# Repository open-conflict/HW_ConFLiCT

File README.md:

HW_ConFLiCT
===========

ConFLiCT

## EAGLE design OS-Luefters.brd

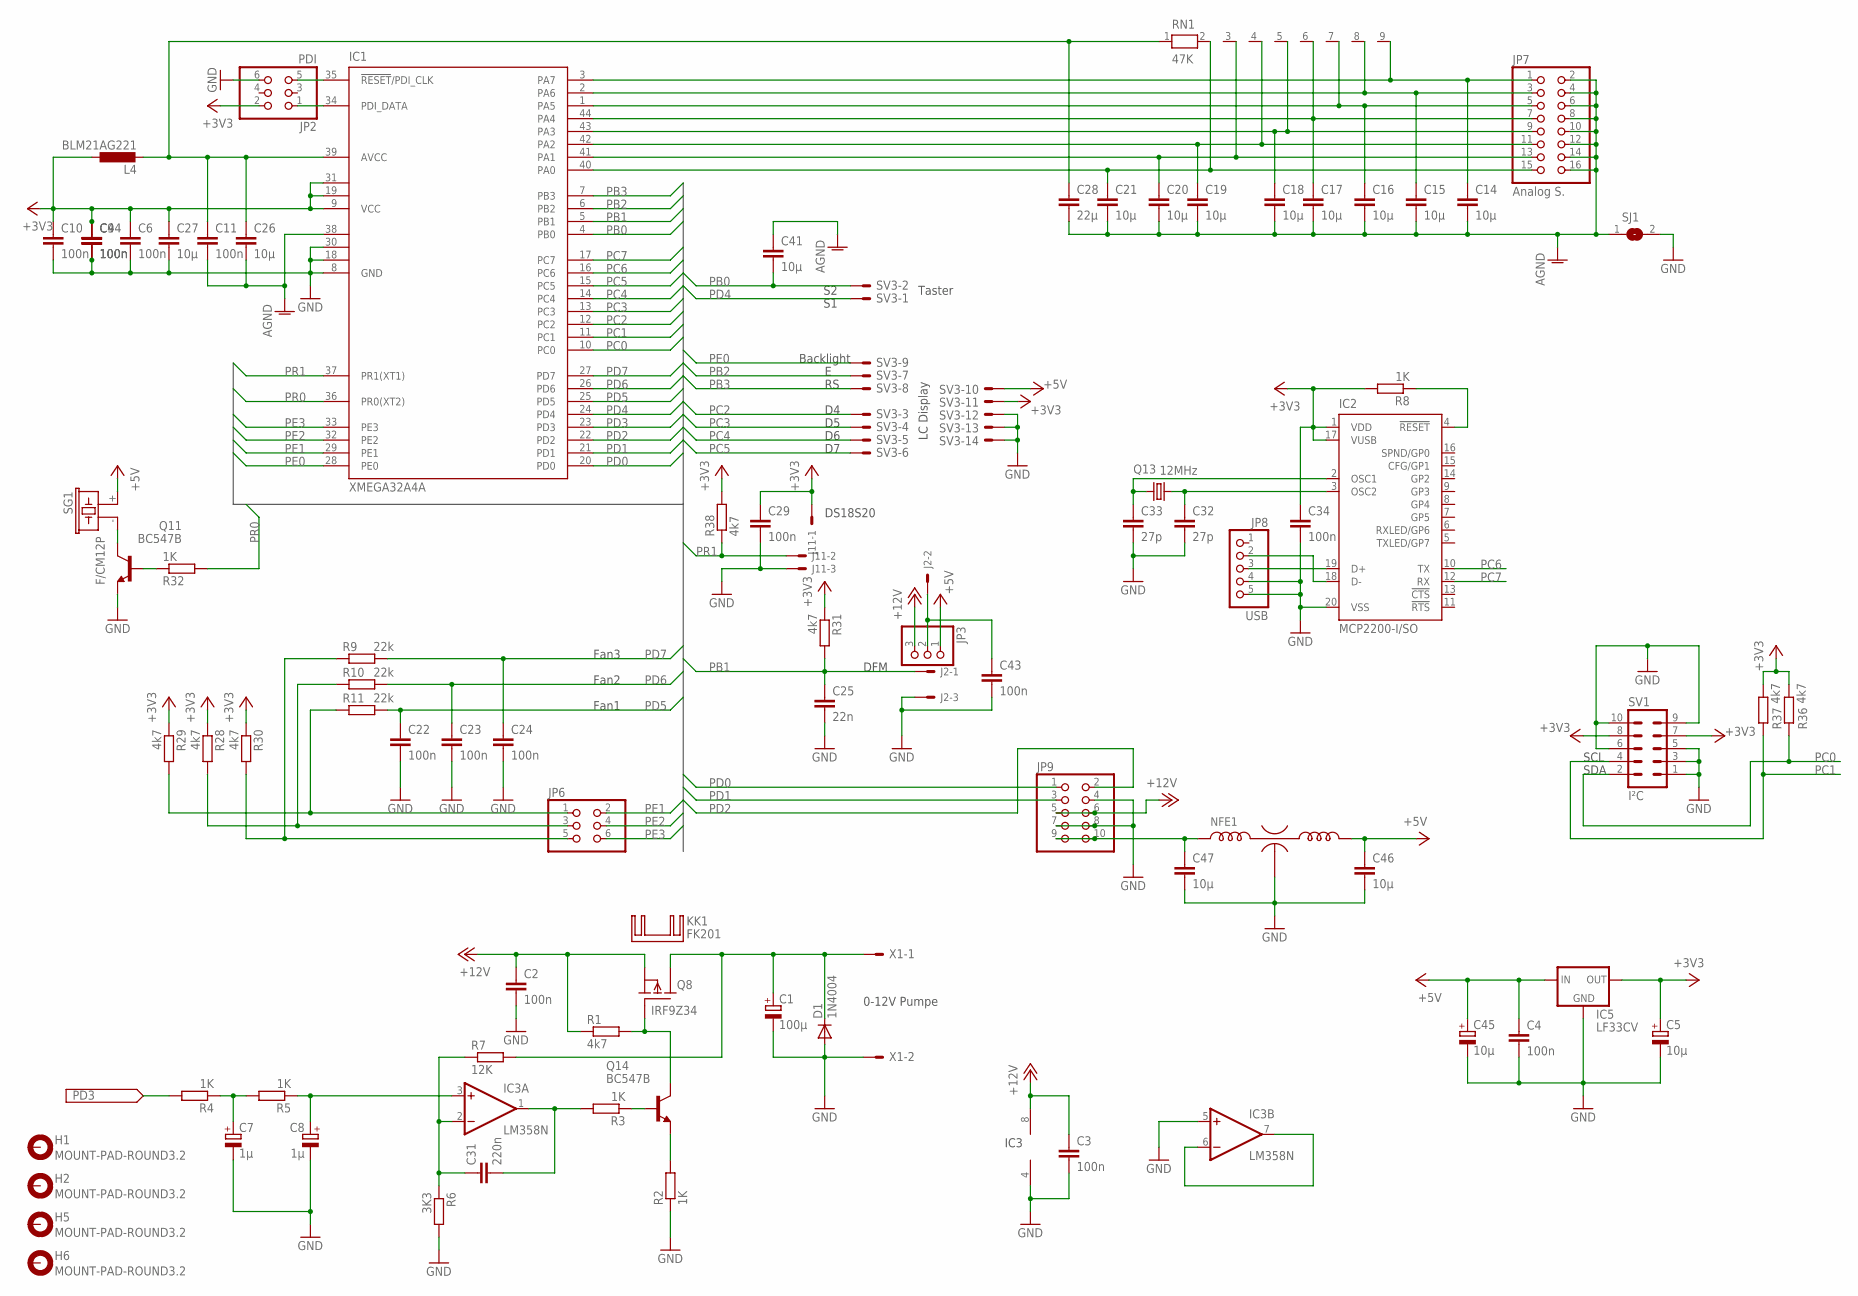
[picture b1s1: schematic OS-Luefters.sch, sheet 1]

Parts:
C1: 100µ; E2,5-7
C2, C3, C4, C22, C23, C24, C34, C43: 100n; C050-025X075
C5, C45: 10µ; E2-5
C6, C9, C10, C11, C29, C44: 100n; C0805K
C7, C8: 1µ; E2-5
C14, C15, C16, C17, C18, C19, C20, C21, C26, C27, C41, C46, C47: 10µ; C0805K
C25: 22n; C050-025X075
C28: 22µ; C0805K
C31: 220n; C050-025X075
C32, C33: 27p; C025-024X044
D1: 1N4004; DO41-10
H1, H2, H5, H6: MOUNT-PAD-ROUND3.2; 3,2-PAD
IC1: XMEGA32A4A; TQFP44
IC2: MCP2200-I/SO; SO-20W
IC3: LM358N; DIL08
IC5: LF33CV; 78XXL
J2, J11: 22-05-7038-03; 7395-03
JP2: PDI; 2X03
JP3: PINHD-1X3/90; 1X03/90
JP6: PINHD-2X3; 2X03
JP7: Analog S.; 2X08/90
JP8: USB; 1X05/90
JP9: PINHD-2X5; 2X05
KK1: FK201
L4: BLM21AG221; L2825P
NFE1: NFE61; 2706
Q8: IRF9Z34; TO220S
Q11, Q14: BC547B; TO92
Q13: 12MHz; HC49U-V
R1, R28, R29, R30, R31, R36, R37, R38: 4k7; 0207/10
R2, R3, R4, R5, R8, R32: 1K; 0207/10
R6: 3K3; 0207/10
R7: 12K; 0207/10
R9, R10, R11: 22k; 0207/10
RN1: 47K; RN-9
SG1: F/CM12P
SJ1: SJ
SV1: I²C; ML10
SV3: ML14E; ML14
X1: AKL18X-02W-NO; AKL182-02-NO

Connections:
+3V3: C5.+, C6.1, C9.1, C10.1, C27.1, C29.1, C34.1, C44.1, IC1.9 (VCC), IC1.19 (VCC1), IC1.31 (VCC2), IC2.1 (VDD), IC2.17 (VUSB), IC5.OUT, J11.1, JP2.2, L4.1, R8.2, R28.1, R29.1, R30.1, R31.1, R36.2, R37.2, R38.2, SV1.7, SV1.8, SV3.11
+5V: C4.1, C45.+, C46.1, IC5.IN, JP3.1, NFE1.OUT, SG1.+ (1), SV3.10
+12V: C2.1, C3.1, IC3.8 (V+), JP3.3, JP9.5, JP9.6, Q8.3 (S), R1.1
AGND: C11.2, C14.2, C15.2, C16.2, C17.2, C18.2, C19.2, C20.2, C21.2, C26.2, C28.2, C41.1, IC1.38 (GND3), JP7.2, JP7.4, JP7.6, JP7.8, JP7.10, JP7.12, JP7.14, JP7.16, SJ1.1
GND: C1.-, C2.2, C3.2, C4.2, C5.-, C6.2, C7.-, C8.-, C9.2, C10.2, C22.2, C23.2, C24.2, C25.2, C27.2, C29.2, C32.2, C33.2, C34.2, C43.2, C44.2, C45.-, C46.2, C47.2, D1.A, IC1.8 (GND), IC1.18 (GND1), IC1.30 (GND2), IC2.20 (VSS), IC3.4 (V-), IC3.5 (+IN), IC5.GND, J2.3, J11.3, JP2.6, JP8.4, JP8.5, JP9.4, JP9.7, JP9.8, NFE1.GND, Q11.1 (E), R2.1, R6.2, SJ1.2, SV1.1, SV1.3, SV1.5, SV1.6, SV1.9, SV1.10, SV3.12, SV3.13, SV3.14, X1.P$2
unnamed: C1.+, D1.C, Q8.2 (D), R7.2, X1.P$1
unnamed: IC3.6 (-IN), IC3.7 (OUT)
unnamed: C43.1, J2.2, JP3.2
unnamed: C7.+, R4.1, R5.2
unnamed: Q8.1 (G), Q14.3 (C), R1.2
unnamed: Q14.1 (E), R2.2
unnamed: C8.+, IC3.3 (+IN), R5.1
unnamed: IC1.34 (PDI_DATA), JP2.1
unnamed: IC1.35 (!RESET!/PDI_CLK), JP2.5
unnamed: C14.1, IC1.3 (PA7), JP7.1, RN1.9
unnamed: C15.1, IC1.2 (PA6), JP7.3, RN1.8
unnamed: C16.1, IC1.1 (PA5), JP7.5, RN1.7
unnamed: C17.1, IC1.44 (PA4), JP7.7, RN1.6
unnamed: C18.1, IC1.43 (PA3), JP7.9, RN1.5
unnamed: C19.1, IC1.42 (PA2), JP7.11, RN1.4
unnamed: C20.1, IC1.41 (PA1), JP7.13, RN1.3
unnamed: C21.1, IC1.40 (PA0), JP7.15, RN1.2
unnamed: Q11.3 (C), SG1.- (2)
unnamed: Q11.2 (B), R32.1
unnamed: C47.1, JP9.9, JP9.10, NFE1.IN
unnamed: Q14.2 (B), R3.1
unnamed: C31.2, IC3.1 (OUT), R3.2
unnamed: C31.1, IC3.2 (-IN), R6.1, R7.1
unnamed: C11.1, C26.1, C28.1, IC1.39 (AVCC), L4.2, RN1.1
unnamed: JP6.5, R9.1, R30.2
unnamed: C32.1, IC2.3 (OSC2), Q13.2
unnamed: C33.1, IC2.2 (OSC1), Q13.1
unnamed: JP6.3, R10.1, R28.2
unnamed: IC2.18 (D-), JP8.2
unnamed: IC2.19 (D+), JP8.3
unnamed: IC2.4 (!RESET), R8.1
unnamed: JP6.1, R11.1, R29.2
PB0: C41.2, IC1.4 (PB0), SV3.2
PB1: C25.1, IC1.5 (PB1), J2.1, R31.2
PB2: IC1.6 (PB2), SV3.7
PB3: IC1.7 (PB3), SV3.8
PC0: IC1.10 (PC0), R36.1, SV1.2
PC1: IC1.11 (PC1), R37.1, SV1.4
PC2: IC1.12 (PC2), SV3.3
PC3: IC1.13 (PC3), SV3.4
PC4: IC1.14 (PC4), SV3.5
PC5: IC1.15 (PC5), SV3.6
PC6: IC1.16 (PC6), IC2.10 (TX)
PC7: IC1.17 (PC7), IC2.12 (RX)
PD0: IC1.20 (PD0), JP9.1
PD1: IC1.21 (PD1), JP9.3
PD2: IC1.22 (PD2), JP9.2
PD3: IC1.23 (PD3), R4.2
PD4: IC1.24 (PD4), SV3.1
PD5: C22.1, IC1.25 (PD5), R11.2
PD6: C23.1, IC1.26 (PD6), R10.2
PD7: C24.1, IC1.27 (PD7), R9.2
PE0: IC1.28 (PE0), SV3.9
PE1: IC1.29 (PE1), JP6.2
PE2: IC1.32 (PE2), JP6.4
PE3: IC1.33 (PE3), JP6.6
PR0: IC1.36 (PR0(XT2)), R32.2
PR1: IC1.37 (PR1(XT1)), J11.2, R38.1

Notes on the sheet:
0-12V Pumpe
DFM
SDA
SCL
DS18S20
LC Display
Taster
IC3
Backlight
Fan1
Fan2
Fan3

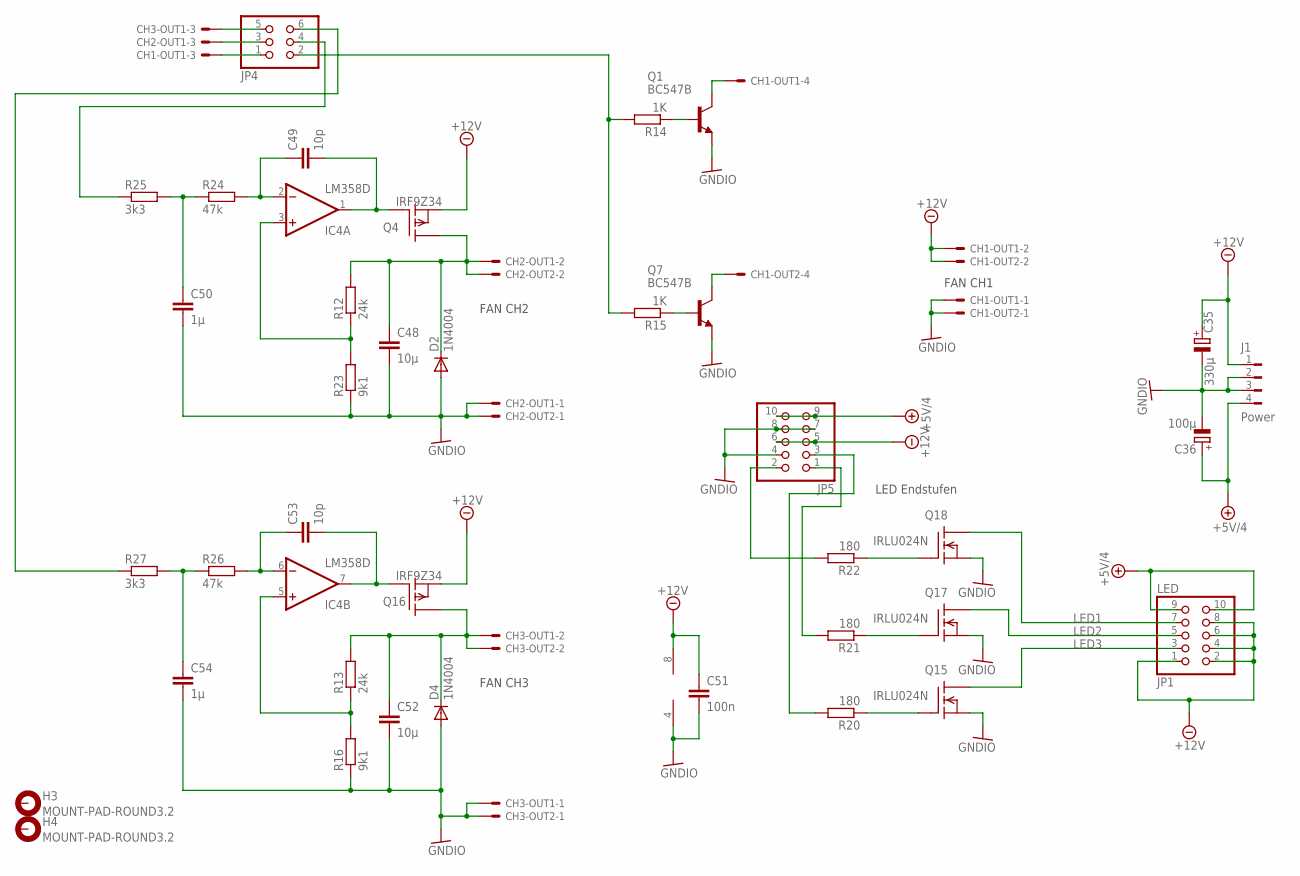
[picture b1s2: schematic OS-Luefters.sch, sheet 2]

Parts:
C35: 330µ; E3,5-8
C36: 100µ; E2,5-7
C48, C52: 10µ; C0805K
C49, C53: 10p; C0805K
C50, C54: 1µ; C0805K
C51: 100n; C0805K
CH1-OUT1, CH1-OUT2: 22-FAN-INTEL-04; 7395-04INTEL
CH2-OUT1, CH2-OUT2, CH3-OUT1, CH3-OUT2: 22-FAN-03; 7395-03MIRROR
D2, D4: 1N4004; DO41-10
H3, H4: MOUNT-PAD-ROUND3.2; 3,2-PAD
IC4: LM358D; SO08
J1: Power; 827001
JP1: LED; 2X05/90
JP4: PINHD-2X3; 2X03
JP5: PINHD-2X5; 2X05
Q1, Q7: BC547B; TO92
Q4, Q16: IRF9Z34; TO220
Q15, Q17, Q18: IRLU024N; I-PAK_TO251AS
R12, R13: 24k; M1206
R14, R15: 1K; M1206
R16, R23: 9k1; M1206
R20, R21, R22: 180; 0207/10
R24, R26: 47k; M0805
R25, R27: 3k3; M0805

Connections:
+5V/4: C36.+, J1.4, JP1.9, JP1.10, JP5.9, JP5.10
-12V: C35.+, C51.1, CH1-OUT1.2, CH1-OUT2.2, IC4.8 (V+), J1.1, JP1.1, JP1.2, JP1.4, JP1.6, JP1.8, JP5.5, JP5.6, Q4.3 (S), Q16.3 (S)
GNDIO: C35.-, C36.-, C48.2, C50.2, C51.2, C52.2, C54.2, CH1-OUT1.1, CH1-OUT2.1, CH2-OUT1.1, CH2-OUT2.1, CH3-OUT1.1, CH3-OUT2.1, D2.A, D4.A, IC4.4 (V-), J1.2, J1.3, JP5.4, JP5.7, JP5.8, Q1.1 (E), Q7.1 (E), Q15.3 (S), Q17.3 (S), Q18.3 (S), R16.1, R23.1
LED1: JP1.7, Q18.2 (D)
LED2: JP1.5, Q17.2 (D)
LED3: JP1.3, Q15.2 (D)
unnamed: C52.1, CH3-OUT1.2, CH3-OUT2.2, D4.C, Q16.2 (D), R13.2
unnamed: JP4.6, R27.1
unnamed: IC4.3 (+IN), R12.1, R23.2
unnamed: C49.2, IC4.1 (OUT), Q4.1 (G)
unnamed: JP4.2, R14.2, R15.2
unnamed: JP4.4, R25.1
unnamed: CH2-OUT1.3, JP4.3
unnamed: CH3-OUT1.3, JP4.5
unnamed: IC4.5 (+IN), R13.1, R16.2
unnamed: C49.1, IC4.2 (-IN), R24.2
unnamed: Q1.2 (B), R14.1
unnamed: C48.1, CH2-OUT1.2, CH2-OUT2.2, D2.C, Q4.2 (D), R12.2
unnamed: Q7.2 (B), R15.1
unnamed: CH1-OUT1.4, Q1.3 (C)
unnamed: C53.2, IC4.7 (OUT), Q16.1 (G)
unnamed: CH1-OUT2.4, Q7.3 (C)
unnamed: CH1-OUT1.3, JP4.1
unnamed: JP5.2, R22.2
unnamed: JP5.1, R21.2
unnamed: JP5.3, R20.2
unnamed: C50.1, R24.1, R25.2
unnamed: C53.1, IC4.6 (-IN), R26.2
unnamed: C54.1, R26.1, R27.2
unnamed: Q15.1 (G), R20.1
unnamed: Q17.1 (G), R21.1
unnamed: Q18.1 (G), R22.1

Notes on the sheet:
LED Endstufen
FAN CH3
FAN CH1
FAN CH2

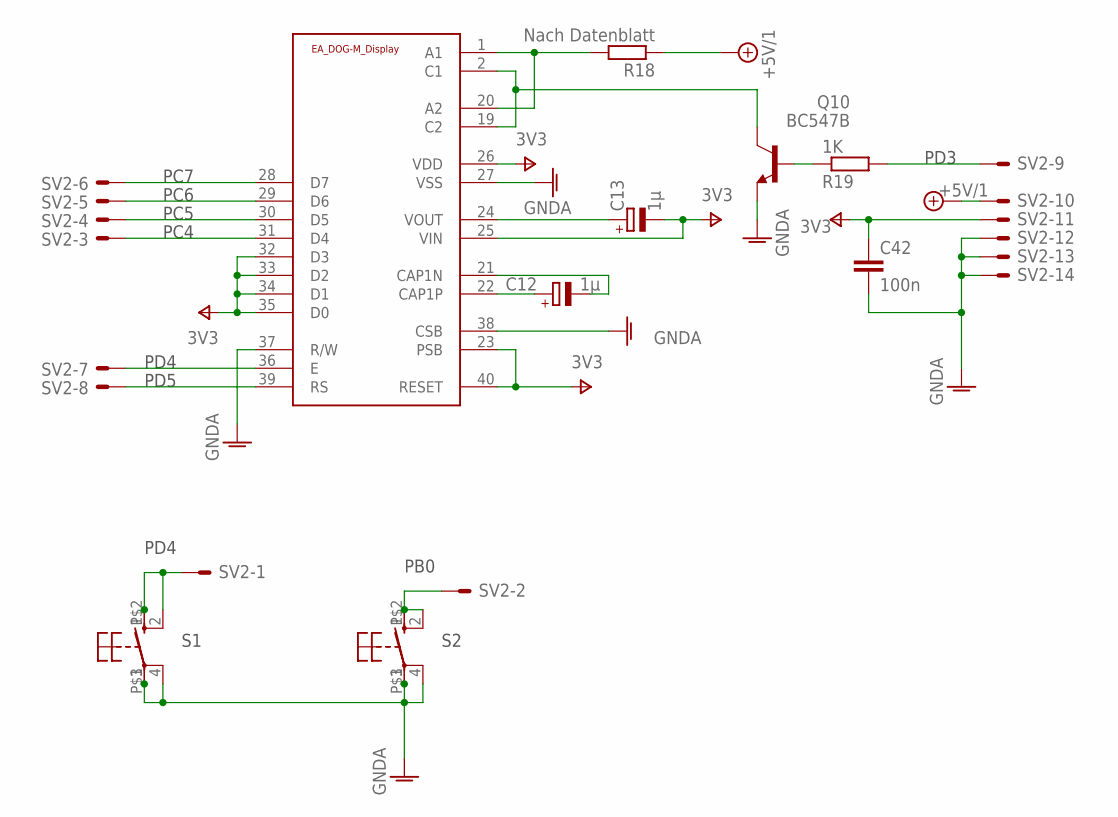
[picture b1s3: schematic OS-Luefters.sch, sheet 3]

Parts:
C12, C13: 1µ; E2-5
C42: 100n; C0805K
Q10: BC547B; TO92
R18: Nach Datenblatt; 0207/10
R19: 1K; 0207/10
S1, S2: 10-XX; B3F-10XX
S3, S4: MTG1/2"
SV2: ML14E; ML14
U$1: EA_DOG-M_DISPLAY; E_DOG-M_DISPLAY

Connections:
+5V/1: R18.1, SV2.10
GNDA: C42.2, Q10.1 (E), S1.3, S1.4 (P1), S2.3, S2.4 (P1), S3.P$1, S4.P$1, SV2.12, SV2.13, SV2.14, U$1.27 (VSS), U$1.37 (R/W), U$1.38 (CSB)
unnamed: R18.2, U$1.1 (A1), U$1.20 (A2)
unnamed: Q10.3 (C), U$1.2 (C1), U$1.19 (C2)
unnamed: Q10.2 (B), R19.1
unnamed: C12.+, U$1.22 (CAP1P)
unnamed: C12.-, U$1.21 (CAP1N)
unnamed: C13.+, U$1.24 (VOUT)
unnamed: S1.1 (S), S1.2 (S1), S3.P$2 (S), SV2.1
unnamed: S2.1 (S), S2.2 (S1), S4.P$2 (S), SV2.2
unnamed: SV2.3, U$1.31 (D4)
unnamed: SV2.4, U$1.30 (D5)
unnamed: SV2.5, U$1.29 (D6)
unnamed: SV2.6, U$1.28 (D7)
unnamed: SV2.7, U$1.36 (E)
unnamed: SV2.8, U$1.39 (RS)
unnamed: R19.2, SV2.9
V+: C13.-, C42.1, SV2.11, U$1.23 (PSB), U$1.25 (VIN), U$1.26 (VDD), U$1.32 (D3), U$1.33 (D2), U$1.34 (D1), U$1.35 (D0), U$1.40 (RESET)

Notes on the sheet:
PC4
PC5
PC6
PC7
PD3
PD4
PD5
PB0

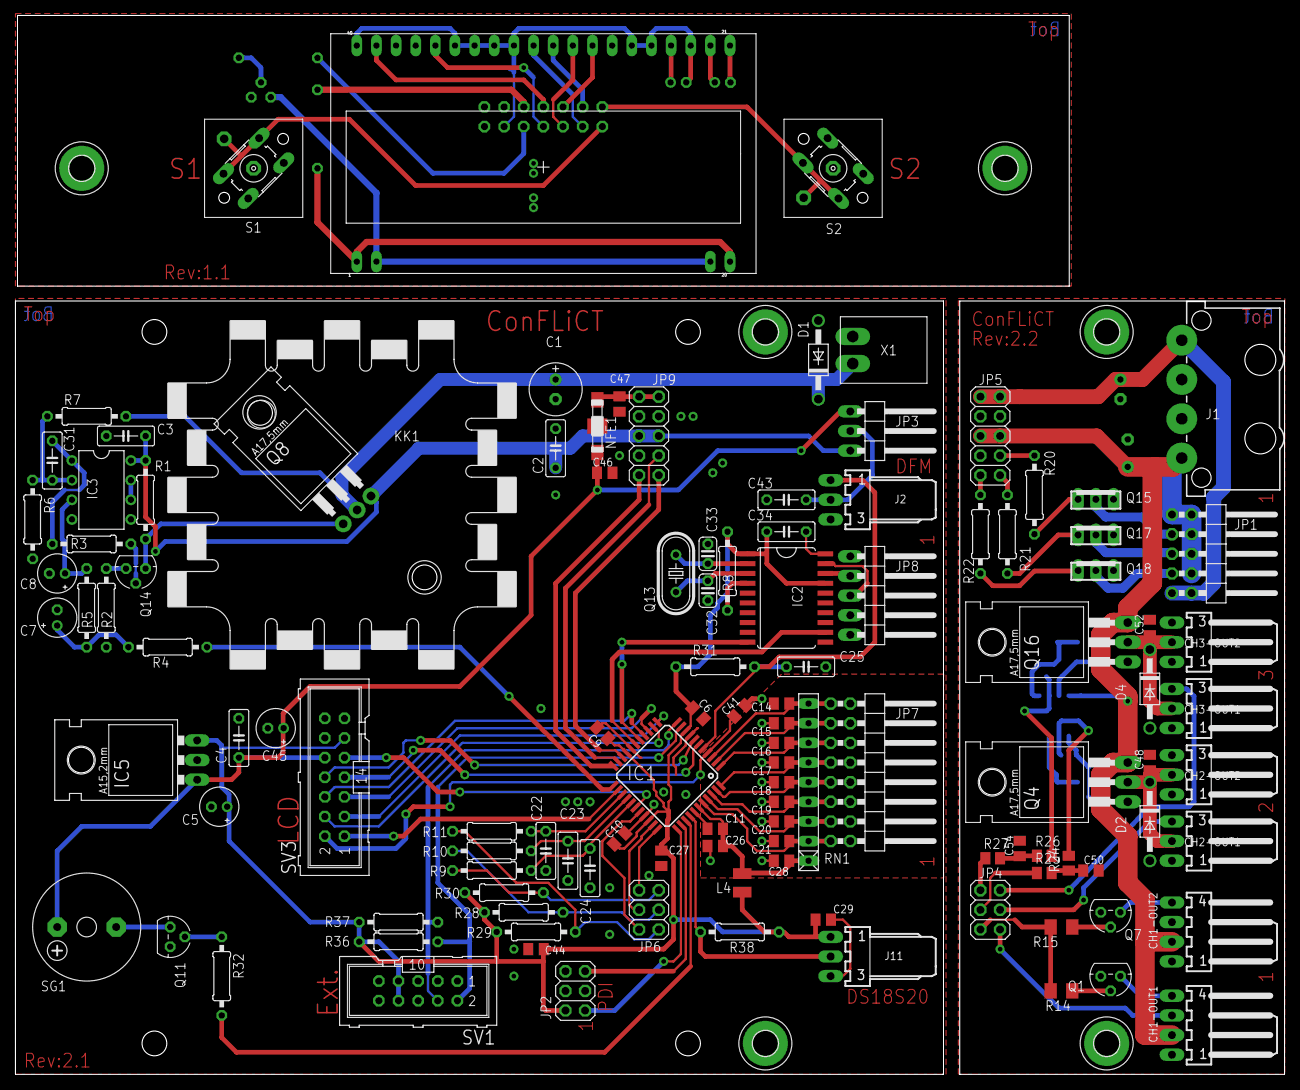
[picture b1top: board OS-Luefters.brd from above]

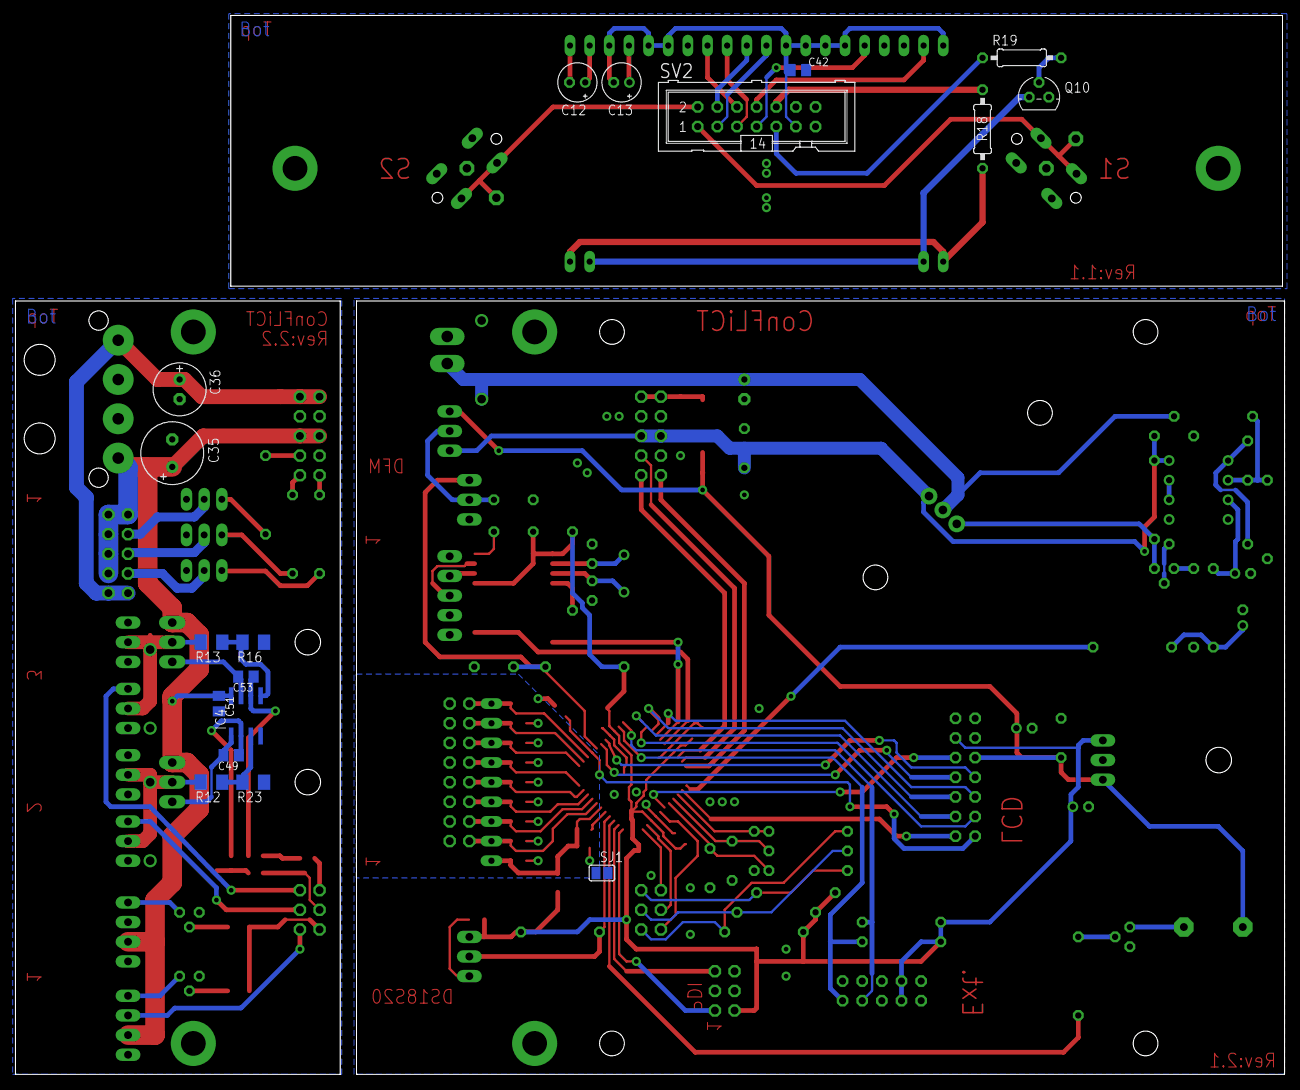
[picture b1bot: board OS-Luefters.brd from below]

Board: 2 copper layers, 164.1 x 136.9 mm, 142 parts (18 on the bottom side), 113 nets.

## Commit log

2014-04-09 init add
